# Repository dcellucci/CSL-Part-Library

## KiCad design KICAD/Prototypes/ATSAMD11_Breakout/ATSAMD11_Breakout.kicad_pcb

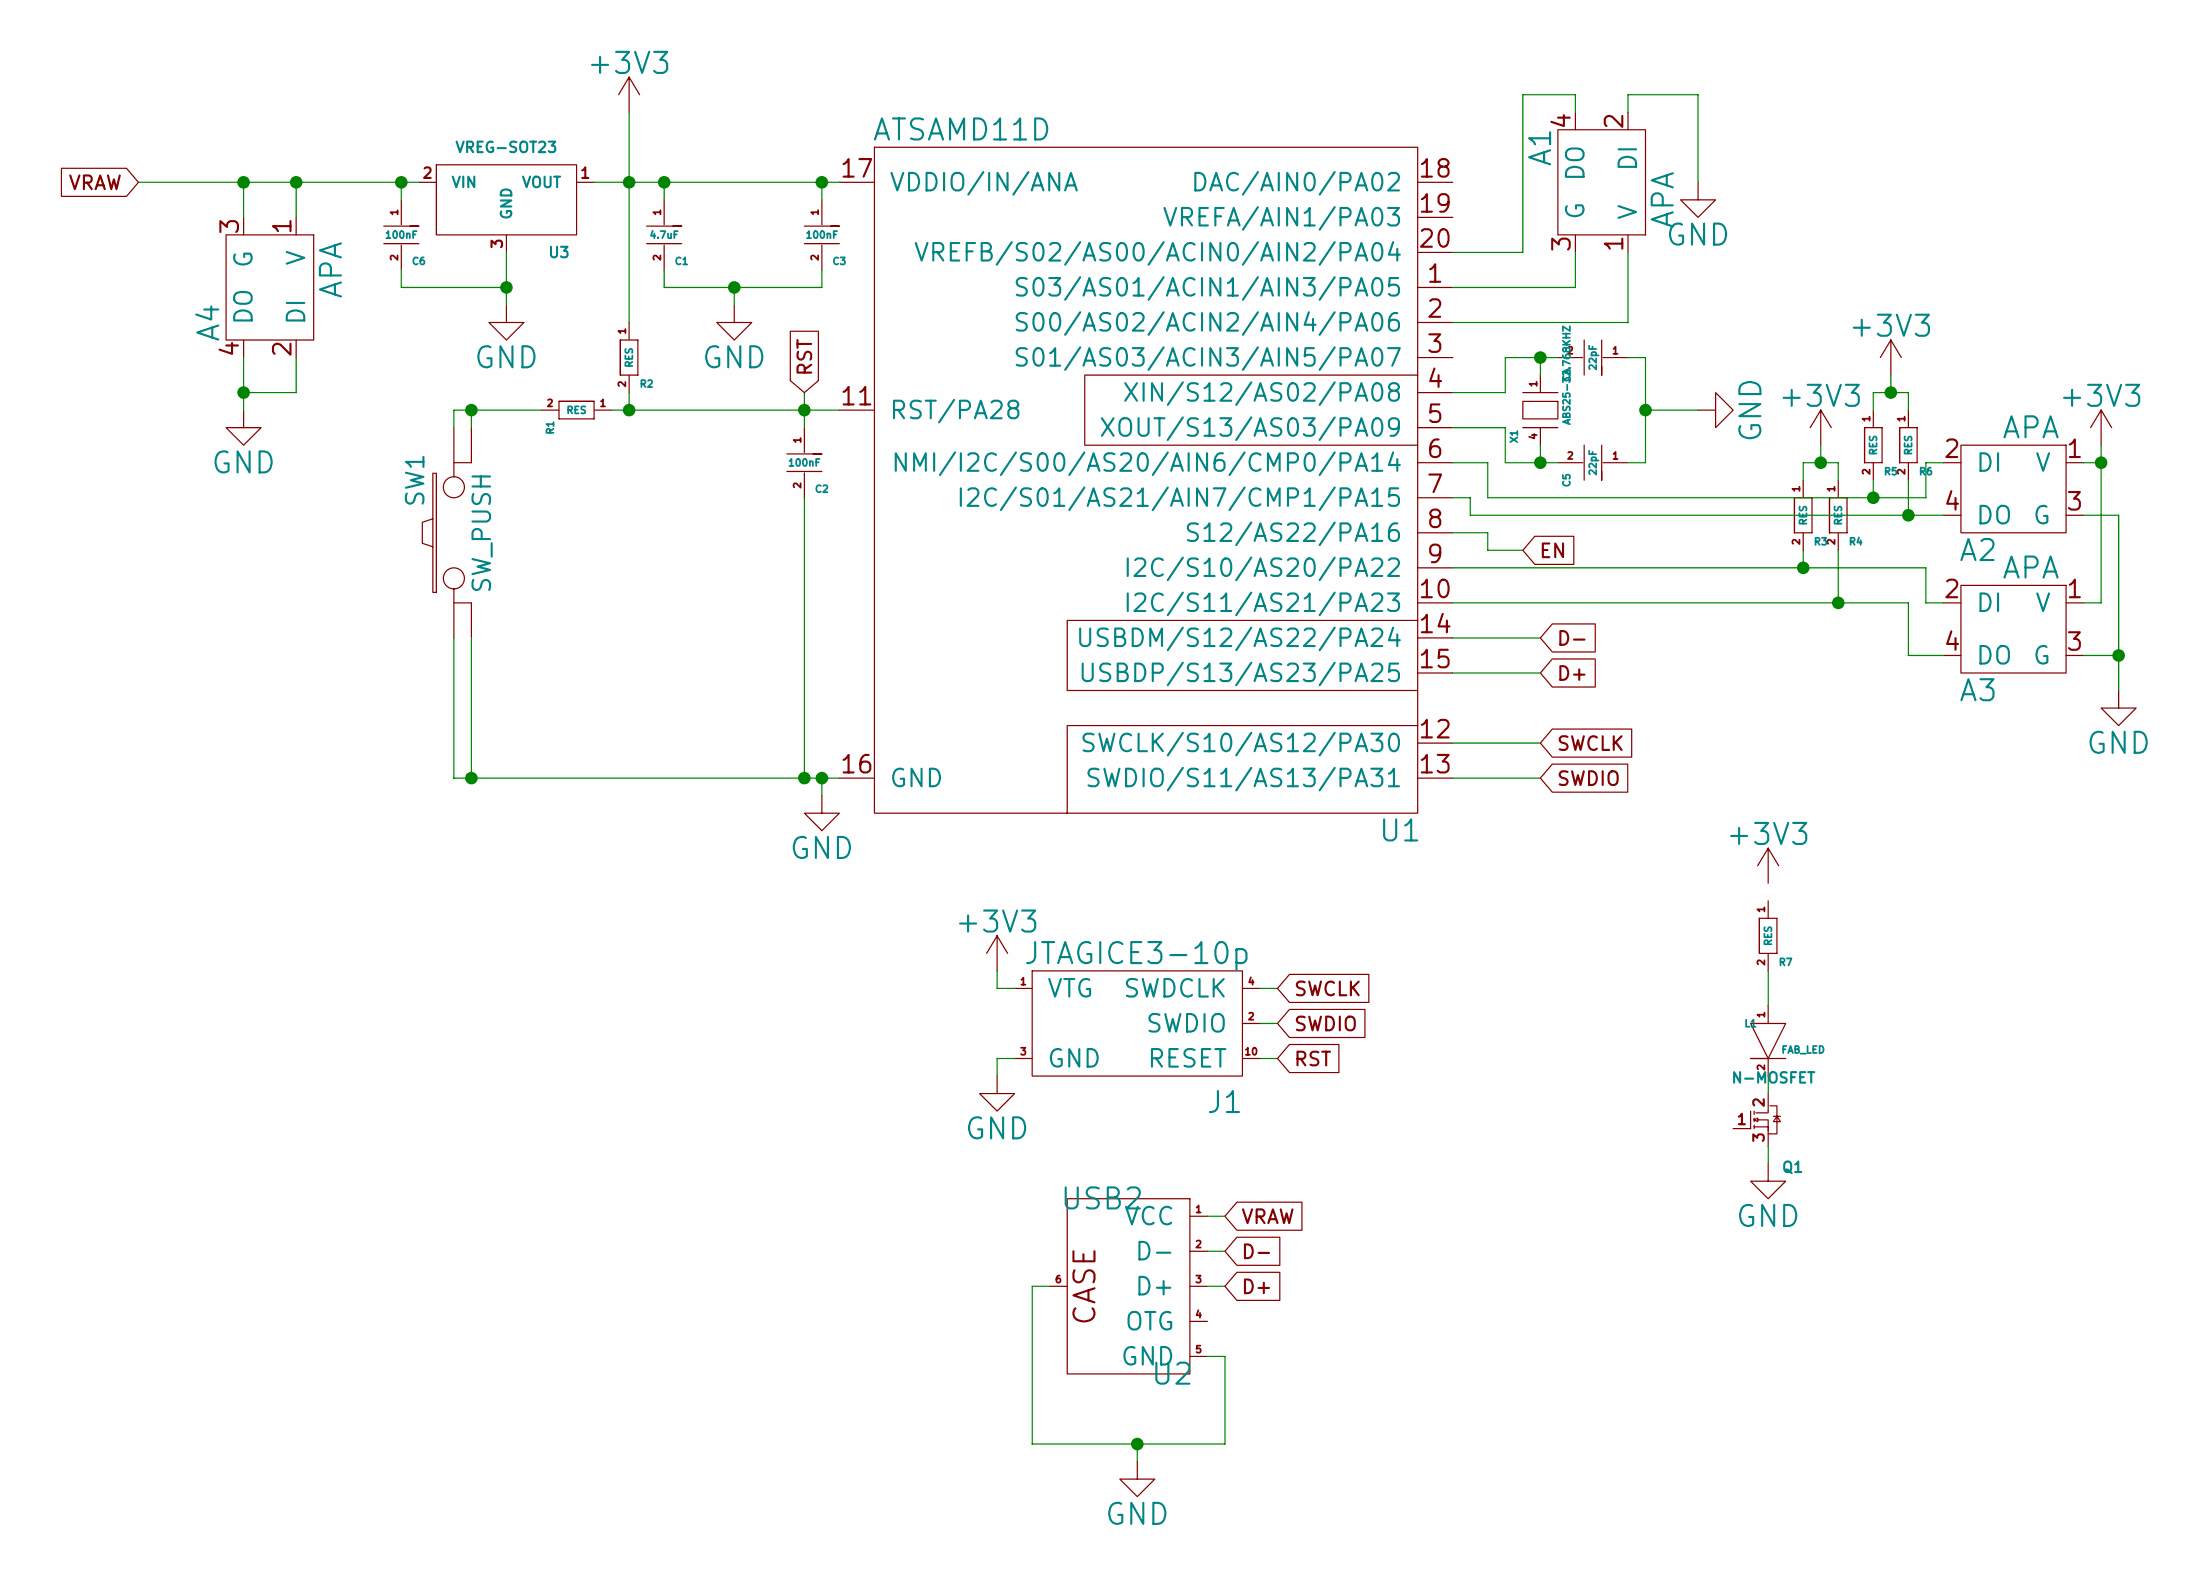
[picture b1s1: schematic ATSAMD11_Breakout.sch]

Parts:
A1, A2, A3, A4: APA; SMD-Header-2x2
C1: 4.7uF; CAP_1206_FAB
C2, C3, C6: 100nF; CAP_1206_FAB
C4, C5: 22pF; CAP_1206_FAB
J1: JTAGICE3-10p
L1: FAB_LED; LED_1206_FAB
Q1: N-MOSFET; SOT-23
R1, R2, R3, R4, R5, R6, R7: RES; CAP_1206_FAB
SW1: SW_PUSH; Switch-Tactile-B3SN-3112P
U1: ATSAMD11D; SOIC-20W_7.5x12.8mm_Pitch1.27mm
U2: USB2; USBMINIB2.0
U3: VREG-SOT23; SOT-23
X1: ABS25-32.768KHZ; 4-SOJ

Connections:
+3V3: A2.1 (V), A3.1 (V), C1.1, C3.1, J1.1 (VTG), R2.1, R3.1, R4.1, R5.1, R6.1, R7.1, U1.17 (VDDIO/IN/ANA), U3.1 (VOUT)
D+: U1.15 (USBDP/S13/AS23/PA25), U2.3 (D+)
D-: U1.14 (USBDM/S12/AS22/PA24), U2.2 (D-)
EN: Q1.1, U1.8 (S12/AS22/PA16)
GND: A1.2 (DI), A2.3 (G), A3.3 (G), A4.2 (DI), A4.4 (DO), C1.2, C2.2, C3.2, C4.1, C5.1, C6.2, J1.3 (GND), Q1.3, SW1.1, SW1.2, U1.16 (GND), U2.5 (GND), U2.6, U3.3 (GND)
unnamed: A1.1 (V), U1.2 (S00/AS02/ACIN2/AIN4/PA06)
unnamed: A1.3 (G), U1.1 (S03/AS01/ACIN1/AIN3/PA05)
unnamed: A1.4 (DO), U1.20 (VREFB/S02/AS00/ACIN0/AIN2/PA04)
unnamed: A2.2 (DI), R5.2, U1.6 (NMI/I2C/S00/AS20/AIN6/CMP0/PA14)
unnamed: A2.4 (DO), R6.2, U1.7 (I2C/S01/AS21/AIN7/CMP1/PA15)
unnamed: A3.2 (DI), R3.2, U1.9 (I2C/S10/AS20/PA22)
unnamed: A3.4 (DO), R4.2, U1.10 (I2C/S11/AS21/PA23)
unnamed: C4.2, U1.4 (XIN/S12/AS02/PA08), X1.1
unnamed: C5.2, U1.5 (XOUT/S13/AS03/PA09), X1.4
unnamed: L1.1, R7.2
unnamed: L1.2, Q1.2
unnamed: R1.2, SW1.3, SW1.4
RST: C2.1, J1.10 (RESET), R1.1, R2.2, U1.11 (RST/PA28)
SWCLK: J1.4 (SWDCLK), U1.12 (SWCLK/S10/AS12/PA30)
SWDIO: J1.2 (SWDIO), U1.13 (SWDIO/S11/AS13/PA31)
VRAW: A4.1 (V), A4.3 (G), C6.1, U2.1 (VCC), U3.2 (VIN)

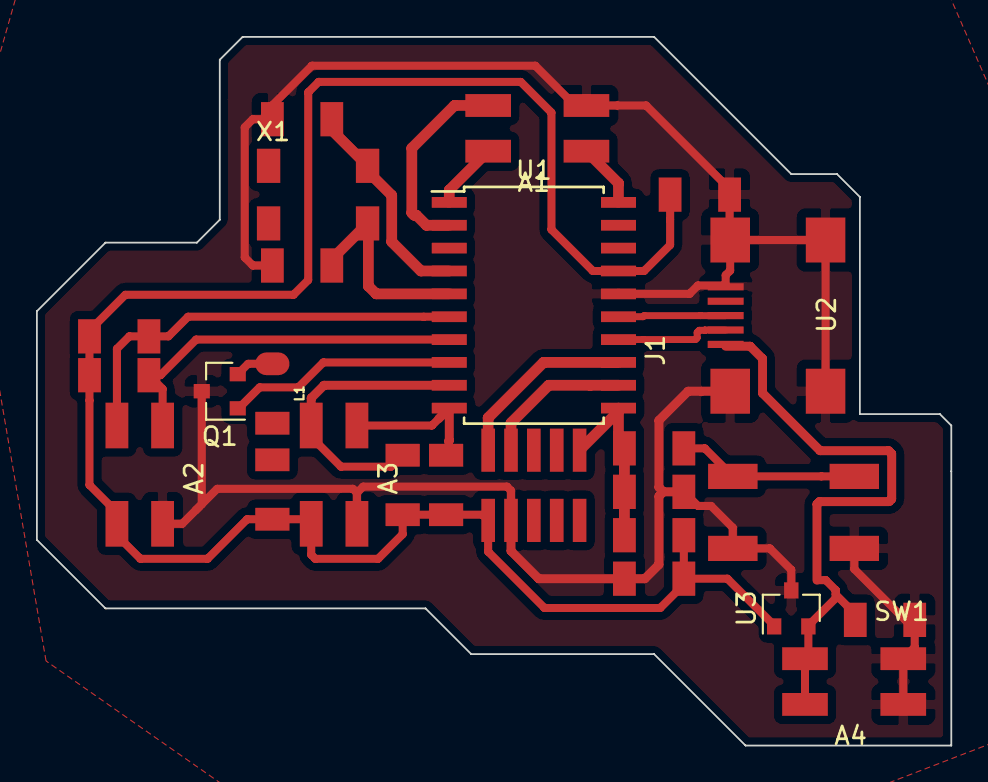
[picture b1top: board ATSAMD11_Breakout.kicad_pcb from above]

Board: 2 copper layers, 50.8 x 39.4 mm, 25 parts (0 on the bottom side), 21 nets.

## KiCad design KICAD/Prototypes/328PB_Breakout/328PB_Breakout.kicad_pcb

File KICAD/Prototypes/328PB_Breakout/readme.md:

### Notes

 1) The fab resonator does not work. Tried both 8 MHz and 20 MHz - possible cause is that the capacitance of the resonator is too high. Trying replacement with lower capacitance (15 pF vs 22 pF)
 2) Programmable with Atmel Studio + Atmel ICE ISP after changing fuses to use internal RC oscillator
 3) Need to check if this fix works for AVRDUDE, etc.

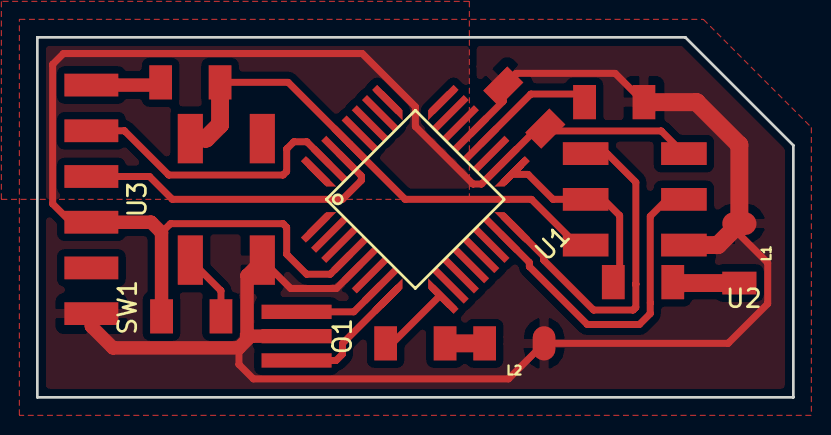
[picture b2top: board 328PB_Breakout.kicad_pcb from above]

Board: 2 copper layers, 42.0 x 20.0 mm, 13 parts (0 on the bottom side), 15 nets.

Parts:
C1, C2, C3: 0.1uF; CAP_1206_FAB
L1, L2: FAB_LED; LED_1206_FAB
O1: RESONATOR
R1, R3: 330; CAP_1206_FAB
R2: 10k; CAP_1206_FAB
SW1: SW_PUSH; Switch-Tactile-B3SN-3112P
U1: ATMEGA328PB; TQFP-32-Fab
U2: AVRISP; SMD-Header-3x2
U3: FTDI; SMD_RA_1x06_No_Holes

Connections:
+5V: C1.1, R2.1, U1.4, U1.18, U2.2, U3.3
DTR: C3.1, U3.6
GND: C1.2, C2.2, L1.2, L2.2, O1.2, SW1.3, SW1.4, U1.5, U1.21, U2.6, U3.1
MISO: U1.16, U2.1
MOSI: U1.15, U2.4
unnamed: C2.1, U1.20
unnamed: L1.1, R1.2
unnamed: L2.1, R3.2
unnamed: O1.1, U1.8
unnamed: O1.3, U1.7
unnamed: R3.1, U1.9
RESET: C3.2, R2.2, SW1.1, SW1.2, U1.29, U2.5
RX: U1.30, U3.4
SCK: R1.1, U1.17, U2.3
TX: U1.31, U3.5

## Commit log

2016-11-20 first KiCad library things
2016-12-25 Split up CSL libraries
2016-12-27 Added a new library for specifically non hand-solderable footprints
2017-01-10 Added an experiment + APA test board
2017-01-11 Added 328PB breakout
2017-01-12 rerouted 328pb breakout
2017-01-13 added 328PB notes
2017-01-20 Added DPS310 library
2017-02-09 Added Power and MOJO parts
2017-02-09 Added ATSAMD11 breakout
2017-02-10 Provided clearance for USB cable
2017-02-23 added INA3221
2017-04-04 added RTC library, board defs derived from Mattairtech
2017-04-04 removed stray diff line
2017-04-06 fixed RTC lib
2017-04-21 added servo calibration jig + APA lib v0
2017-04-23 finished APA lib
